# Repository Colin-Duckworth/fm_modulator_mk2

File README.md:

FM Modulator Project

This project is to make a colpitts oscillator based fm modulator from the transistor/component level.
It will consist of a common emitter, BJT amplifier, tapped LC tank (to form the oscillator), and emitter follower amp (as buffer) into an antenna feed

In terms of the toolchain, this will be an introduction for me to learn KiCad with its integrated SPICE simulation to build out the schematic.

## Projects

| Folder | Contents | Simulation |
|---|---|---|
| `project_folders/fm_modulator_openloop` | CE stage + tank, driven by an AC source | AC sweep |
| `project_folders/fm_modulator_closedloop` | Colpitts oscillator, RF buffer, varactor FM, mic + audio chain, power input (the board) | TRAN / FFT |

## BOM — `fm_modulator_closedloop` (JLCPCB assembly)

Stock and part type checked on jlcpcb.com on 2026-11-16. **Basic** parts have no setup fee; each unique **Extended** part adds a loading fee (about $3). The `LCSC` field on every symbol holds the part number, so the JLCPCB Tools / Fabrication Toolkit plugins can export the BOM and CPL directly.

| Designator | Qty | Value | Package / footprint | LCSC | Type | Part (manufacturer) | Notes |
|---|---|---|---|---|---|---|---|
| Q101, Q102 | 2 | MMBT3904 | SOT-23 | C20526 | Basic | MMBT3904 (CJ) | Oscillator + buffer; sim model = 2N3904 die |
| U1 | 1 | NE5532 | SOIC-8 | C7426 | Basic | NE5532DR (TI) | Dual op amp: mic diff amp + gain stage |
| U3 | 1 | AMS1117-3.3 | SOT-223 | C6186 | Basic | AMS1117-3.3 (AMS) | 3.3 V for the mic |
| D201 | 1 | SS14 | SMA (DO-214AC) | C2480 | Basic | SS14 (MDD) | Reverse-polarity protection |
| FB201 | 1 | 100 Ω @ 100 MHz | 0805 | C1015 | Basic | GZ2012D101TF (Sunlord) | Supply ferrite |
| R101, R104 | 2 | 510 Ω | 0603 | C23193 | Basic | 0603WAF5100T5E | Was 500 Ω (not a standard value) |
| R102 | 1 | 27 kΩ | 0603 | C22967 | Basic | 0603WAF2702T5E | |
| R103 | 1 | 10 kΩ | 0603 | C25804 | Basic | 0603WAF1002T5E | |
| R105 | 1 | 150 Ω | 0603 | C22808 | Basic | 0603WAF1500T5E | |
| R108 | 1 | 12 kΩ | 0603 | C22790 | Basic | 0603WAF1202T5E | |
| R109 | 1 | 2.7 kΩ | 0603 | C13167 | Basic | 0603WAF2701T5E | |
| R110 | 1 | 22 Ω | 0603 | C23345 | Basic | 0603WAF220JT5E | |
| R111 | 1 | 75 Ω | 0603 | C4275 | Basic | 0603WAF750JT5E | Was 68 Ω (68 Ω is Extended); buffer Ic ≈ 14 mA instead of 15 mA |
| R112 | 1 | 68 Ω | 0603 | C27592 | Extended | 0603WAF680JT5E | Buffer output termination: 68 Ω gives ≈50 Ω output once Cμ feedback is included (51 Ω gave ≈40 Ω) |
| R113 | 1 | 220 Ω | 0603 | C22962 | Basic | 0603WAF2200T5E | |
| R201 | 1 | 47 Ω | 0603 | C23182 | Basic | 0603WAF470JT5E | Audio supply RC filter |
| R202, R203 | 2 | 22 kΩ | 0603 | C31850 | Basic | 0603WAF2202T5E | VMID divider |
| R204, R206 | 2 | 5.1 kΩ | 0603 | C23186 | Basic | 0603WAF5101T5E | Diff amp inputs |
| R205, R207, R208 | 3 | 100 kΩ | 0603 | C25803 | Basic | 0603WAF1003T5E | |
| R209 | 1 | 3.3 kΩ | 0603 | C22978 | Basic | 0603WAF3301T5E | |
| C101, C102 | 2 | 47 pF C0G | 0603 | C1671 | Basic | CL10C470JB8NNNC | Were 50 p / 48 p |
| C103 | 1 | 22 pF C0G | 0603 | C1653 | Basic | CL10C220JB8NNNC | Was 33 p; trimmer now carries the rest |
| C104 | 1 | 33 pF C0G | 0603 | C1663 | Basic | CL10C330JB8NNNC | |
| C106 | 1 | 10 pF C0G | 0603 | C1634 | Basic | CL10C100JB8NNNC | Varactor coupling (was 1 p) |
| C110, C112, C203 | 3 | 1 nF X7R | 0603 | C1588 | Basic | CL10B102KB8NNNC | |
| C111, C202, C205, C209, C212 | 5 | 100 nF X7R | 0603 | C14663 | Basic | CC0603KRX7R9BB104 | |
| C210, C211 | 2 | 1 µF X5R | 0603 | C15849 | Basic | CL10A105KB8NNNC | Mic coupling |
| C201, C204, C206, C207, C213 | 5 | 10 µF 25 V X5R | 0805 | C15850 | Basic | CL21A106KAYNNNE | |
| C208 | 1 | 22 µF 25 V X5R | 0805 | C45783 | Basic | CL21A226MAQNNNE | AMS1117 output |
| C109 | 1 | 2.2 pF C0G | 0603 | C5137608 | Extended | FCC0603N2R2C500CT (FOJAN) | No Basic 2.2 pF exists |
| C105 | 1 | 5.8–20 pF trimmer | TZC3 (4.5×3.2) | C22468122 | Extended | STC3MD20-T1 (SEHWA) | Coarse frequency set (was fixed 3.3 p) |
| L101 | 1 | 1 µH ±5% | 0603 | C127458 | Extended | FHW0603UF1R0JST (FH) | SRF 400 MHz; most 1 µH 0603 parts self-resonate near 100 MHz |
| L102 | 1 | 100 nH ±2% wirewound | 0603 | C98088 | Extended | LQW18ANR10G00D (Murata) | Tank inductor; Q matters more than the setup fee |
| D101 | 1 | 1SV229 | SOD-323 | C2762682 | Extended | 1SV229(TPH3F) (Toshiba) | FM-band varactor |
| U2 | 1 | IM73A135V01 | PG-LLGA-5 (4×3) | C3171831 | Extended | IM73A135V01XTSA1 (Infineon) | Analog differential MEMS mic, bottom port (footprint has the sound hole) |
| RV201 | 1 | 50 kΩ trim | Bourns 3314J | C50895 | Extended | 3314J-1-503E (Bourns) | Deviation / audio gain |
| J1, J2 | 2 | SMA jack, vertical through-hole | Amphenol 132134 pattern (5 pins, 5.08 mm square) | C496549 | Extended | BWSMA-KE-Z001 (BAT Wireless) | J1 = ANT, J2 = TEST. About $0.40 each; JLC solders through-hole parts (wave/hand), or hand-solder them |
| U101 | 1 | PE4259 SPDT RF switch | SC-70-6 | C470892 | Extended | PE4259-63 (pSemi) | TX enable: CTRL high = RFC→RF1 (J1) |
| S101 | 1 | SPDT slide switch | SMD right-angle (Shouhan MSK12C02) | C431540 | Extended | MSK12C02 | STBY / TX, lever overhangs the right edge |
| D202 | 1 | Green LED | 0805 | C2297 | Basic | KT-0805G (KENTO) | PWR (on DC_Bias) |
| D102 | 1 | Red LED | 0603 | C2286 | Basic | KT-0603R (KENTO) | TX |
| R210 | 1 | 4.7 kΩ | 0603 | C23162 | Basic | 0603WAF4701T5E | PWR LED, ≈1.9 mA |
| R115, R117 | 2 | 1 kΩ | 0603 | C21190 | Basic | 0603WAF1001T5E | TX LED (≈1.3 mA); CTRL series resistor |
| R116 | 1 | 100 kΩ | 0603 | C25803 | Basic | 0603WAF1003T5E | TX_EN pull-down (STBY by default) |
| C113, C114 | 2 | 1 nF X7R | 0603 | C1588 | Basic | CL10B102KB8NNNC | PE4259 RF1/RF2 DC blocks |
| C115, C116 | 2 | 100 nF X7R | 0603 | C14663 | Basic | CC0603KRX7R9BB104 | U101 VDD decoupling; CTRL filter |
| TP3, TP4 | 2 | Test loop | Keystone 5015 SMD | C2906768 | **Hand-solder** | 5015 (Keystone) | MIC_IN, OPAMP_OUT; excluded from JLC BOM/CPL, order separately |
| TP5 | 1 | +12V_IN, red | Keystone 5010 THT | C2906765 | **Hand-solder** | 5010 (Keystone) | Alligator-clip power input; excluded from JLC BOM/CPL, order separately |
| TP6 | 1 | GND, black | Keystone 5011 THT | C238127 | **Hand-solder** | 5011 (Keystone) | Alligator-clip ground; excluded from JLC BOM/CPL, order separately |
| TP1 | 1 | Test pad | 1.0 mm pad | — | — | bare copper | No part to place (excluded from BOM/CPL) |
| R114, V101, V102 | — | — | — | — | — | — | **Simulation only**: excluded from BOM and board |

**Summary (Rev B):** JLC assembles 43 unique parts. 32 are Basic, covering all resistors except R112, all but one fixed capacitor, both transistors, the op amp, the LDO, the diode, the ferrite and both LEDs. 11 are Extended (C109, C105, L101, L102, D101, U2, RV201, J1/J2, R112, U101, S101), roughly $33 in setup fees. J1 and J2 are through-hole parts: JLC assembly adds a through-hole soldering charge, or leave them off the order and hand-solder them like the test loops. The four test loops (TP3–TP6) are hand-soldered: their footprints are on the board, but they're marked *exclude from BOM* and *exclude from position files* in KiCad, so JLC leaves the pads empty. Order them separately (LCSC numbers above, about 2× 5015, 1× 5010 red, 1× 5011 black). TP1 is a bare pad with no part.

## PCB — `fm_modulator_closedloop.kicad_pcb`

### Substrate and stackup (JLCPCB JLC04161H-7628, standard 4-layer FR-4)

| Layer | Use | Material | Thickness | εr |
|---|---|---|---|---|
| L1 — F.Cu | RF and oscillator traces, all parts | 1 oz copper | 0.035 mm | — |
| dielectric 1 | | 7628 prepreg | 0.2104 mm | 4.4 |
| L2 — In1.Cu "GND" | Solid ground plane (no routing) | 0.5 oz copper | 0.0152 mm | — |
| dielectric 2 | | FR-4 core | 1.065 mm | 4.6 |
| L3 — In2.Cu "PWR" | Power: DC_Bias plane + VCC_AUDIO plane | 0.5 oz copper | 0.0152 mm | — |
| dielectric 3 | | 7628 prepreg | 0.2104 mm | 4.4 |
| L4 — B.Cu | Control / audio / signal traces, GND pour | 1 oz copper | 0.035 mm | — |

Total ≈ 1.6 mm; HASL lead-free finish. In the JLC order choose **4 layers, 1.6 mm, Specify Stackup → JLC04161H-7628**.

### 50 Ω RF output (C112 → U101 → J1 / J2)
- **Geometry:** microstrip on L1 referenced to the L2 ground plane, h = 0.2104 mm, t = 0.035 mm, εr = 4.4.
- **Width:** Hammerstad–Jensen with thickness correction gives Z₀ = 50 Ω at **w = 0.373 mm** bare (51.0 Ω at 0.36 mm). Solder mask lowers Z₀ by about 1–2 Ω, so the RF traces are drawn at **0.36 mm** (≈ 50 Ω under mask). Confirm with JLC's impedance calculator before ordering.
- **Length:**
  - C112 → U101 RFC is about 11 mm, a straight run across the BUFFER AMP / TX SWITCH boundary.
  - Each throw (U101 → C113/C114 → J1/J2) is about 9 mm.
  - At 100 MHz that's under 2° (λg ≈ 1.68 m, ε_eff ≈ 3.19), so the lines are electrically short and the match is set by the source and load.
  - The source is the buffer: R112 = 68 Ω gives Z_out ≈ 50 Ω. With the switch's 0.35 dB loss and a 50 Ω load on J1/J2, everything is ≈ 50 Ω.
- **Ground:**
  - J1 and J2 are through-hole, so their four ground posts tie L1, L2 and L4 together right at the connector.
  - U101's GND pin has its own via beside the pin.
  - At these lengths, the L1 pour's normal 0.3 mm clearance to the RF traces has a negligible effect. The old rule-area keep-out and via fence went with the edge-launch connector.
- **Connectors:** J1 (ANT) and J2 (TEST) are vertical through-hole SMA jacks (BWSMA-KE-Z001) on the standard 5-pin pattern (centre pin plus four ground posts on a 5.08 mm square). The cable plugs in perpendicular to the board. The ~1.6 mm the centre pin runs through the stackup is about λ/1000 at 100 MHz, so it doesn't matter.

### Layout
- **Board:** 100 × 62 mm, four M3 mounting holes (3.2 mm NPTH) 3.5 mm in from each corner. Still within JLC's ≤ 100 × 100 mm price tier.
- **Floorplan** (re-laid 2026-11-18): five labelled silkscreen boxes. The top row is four 25 mm columns that follow the signal left → right, and a full-width POWER strip (about 16 mm) runs along the bottom.

  | Box | Parts | Notes |
  |---|---|---|
  | AUDIO (x 100–125) | U2 mic, C209, TP3, C210/C211, R204–R207, U1, C212, R209, C213, RV201, TP4, R202/R203/C206 (VMID) | Widely spaced for probing and rework. Mic at the top, U1 in the middle, AUDIO_OUT (RV201 / TP4) bottom-right facing R208. |
  | OSCILLATOR (x 125–150) | Q101, L101/R101, L102, C101–C106, R102–R105, TP1, D101, R208 | Kept tight (short tank loops), but spaced so no reference designators overlap. The tank output leaves at the bottom-right towards C109. |
  | BUFFER AMP (x 150–175) | C109, Q102, R108–R113, C110–C112 | Generous spacing. The RF line runs straight through at y = 127.5 mm. |
  | TX SWITCH & PORTS (x 175–200) | U101 + C113–C116, R116/R117, J2 TEST (top), J1 ANT (bottom), S101 + D102/R115 (red TX LED) | S101 sits on the right edge with its slider at the edge; silk reads STBY (top) / TX (bottom). |
  | POWER (bottom strip) | TP5 (+12 V) / TP6 (GND) clip posts, D201, FB201, C201–C203, D202 + R210 (green PWR LED), R201, C204/C205, C207, U3, C208 | Input on the right, flowing left: DC_Bias parts, then R201 at x = 150, then the VCC_AUDIO / 3V3 parts. |
- **Routing:**
  - **By script (L1):** RF only. That means the oscillator (including the varactor feed), the buffer, the tank → C109 link, and C112 → U101 → C113/C114 → J1/J2. Also U101's local nets (CTRL via C116/R117, VDD to C115, TX_EN R116 → R117) and GND / DC_Bias pad vias for the RF parts.
  - **By hand:** everything in AUDIO and POWER, plus the TX LED / S101 and the 3V3 and TX_EN runs to the switch column.
- **Vias:** each RF-part GND pad has its own via to L2, and each RF-part DC_Bias pad has a via to the L3 plane. GND stitching runs on a 4 mm grid inside the three RF boxes plus a ring around the board edge.
- **Pours:** L1 GND, L2 GND, L4 GND. L3 is split to match the sections:
  - **VCC_AUDIO:** under the AUDIO column plus the POWER strip left of x = 150 mm.
  - **DC_Bias:** everywhere else (under the OSCILLATOR, BUFFER and TX columns and the right half of the strip).
  - **R201** straddles the split at x = 150 mm in the strip.
- **Net classes:** RF (/RF_Out, /RF_Ant, /RF_Test, U101 RF1/RF2) 0.36 mm, Power (DC_Bias, VCC_AUDIO, 3V3) 0.5 mm, Default 0.25 mm.
- **JLC design rules:** 0.15 mm minimum track and clearance, 0.3/0.6 mm vias, 0.3 mm copper-to-edge.
- **Silkscreen, front:**
  - Five labelled section boxes.
  - Labels for +12V, GND, PWR, ANT (J1), TEST (J2) and STBY/TX at the switch.
  - Reference designators are 0.8 mm (meets the project's text-height rule), horizontal and clear of pads, with 0 silkscreen warnings.
- **Silkscreen, back:**
  - Each section has a short description sitting directly behind it.
  - The stackup (JLC04161H-7628 layer table + 50 Ω width) sits behind the oscillator / buffer boundary.
  - The power-path description and the project tag (name, date, Rev B) are in the POWER strip.

### Still to do in KiCad
DRC after the 2026-11-18 re-layout shows 0 copper/clearance errors, 0 silkscreen warnings and 0 schematic-parity issues. 47 unconnected items are left for hand routing.

1. **Route the non-RF nets.** Prefer L4 for anything crossing an RF box.
   - **Audio:** mic → C210/C211 → R204/R206 → U1, the U1 feedback nets, VMID, and AUDIO_OUT (U1 pin 7 / RV201 / TP4 → R208 in the oscillator box).
   - **Power:** TP5 → D201 → FB201 (wide, L1), DC_Bias and VCC_AUDIO plane vias for the POWER and AUDIO parts, and the PWR LED (R210 → D202).
   - **3V3:** U3 tab → C208 → C209 / U2 VDD, plus a run over to **C115 pad 1** (U101 VDD) and **S101 pin 1**.
   - **TX_EN:** S101 pin 2 → R115 (→ D102) and over to **R116 / R117** beside U101.
2. **Mic ground:** tie U2 pad 5 (centre GND) to pad 4.
3. **Refill zones** (B), then run DRC. The L3 VCC_AUDIO "isolated copper" warning clears once its pads have vias.
4. **Mic hole-clearance error:** one DRC error comes from the Infineon footprint itself (its centre GND pad sits 0.18 mm from its own sound hole). Exclude it in the DRC dialog.
5. **Check S101's direction with a meter** before the first power-up with an antenna: in the **TX** position, pins 2–1 should be connected. The red TX LED always shows the real state, because it hangs off TX_EN itself.
6. **Optional:** Update PCB from Schematic (F8) should report nothing to change; every footprint is linked to its symbol.

## Rev B: power LED and TX-enable switch

> **Status:** in the schematic and on the PCB (2026-11-18). Parts checked on jlcpcb.com on 2026-11-17/18; the PE4259 pinout and truth table were checked against the pSemi datasheet. The rows are in the BOM table above.

### Power indicator (green "PWR")
- **D202** (green 0805) + **R210** (4.7 kΩ) from `DC_Bias` to GND, in the POWER box.
- It sits after D201 and FB201, so it lights only when 12 V is present **and** the polarity is correct.
- Current: (11.65 V − ~2.9 V) / 4.7 kΩ ≈ **1.9 mA**. For a dimmer LED, raise R210 to 10 kΩ (≈ 0.9 mA).

### TX enable (SPDT RF switch after the buffer)
The oscillator and buffer **run all the time**, and only the buffer's output is steered. The tank therefore sees the same load in both positions, so the carrier doesn't jump when you go from tuning to transmitting. (Turning the buffer off instead would pull the carrier and leak 30–40 dB.)

```
                                     ┌─ RF1 ─ C113 1n ─ 50 Ω ─► J1  ANTENNA   (TX)
buffer ─ C112 ─ 50 Ω ─ RFC  U101 PE4259
                                     └─ RF2 ─ C114 1n ─ 50 Ω ─► J2  TEST      (STBY)
                       VDD ◄─ 3V3 (C115 100 nF)
                       CTRL ◄─ R117 1 kΩ ─┬─ TX_EN
                                          C116 100 nF to GND (debounce, keeps RF off the control line)

        3V3 ──o TX
               \___ S101 common ── TX_EN ──┬── R115 1 kΩ ── D102 red "TX" ── GND
        GND ──o STBY                       └── R116 100 kΩ ── GND (STBY if the switch is mid-travel)
```

- **The physical control:** **S101** is a small SMD slide switch (MSK12C02, right-angle). Its lever sticks out past the board edge, and the silkscreen reads **STBY ◄ ► TX**.
  - It drives `TX_EN` hard to 3V3 or GND, so no logic IC is needed.
  - The 100 kΩ pull-down means a broken switch or a mid-travel position defaults to STBY.
- **TX LED:** **D102** (red) hangs straight off `TX_EN`, so it lights exactly when the switch routes RF to the antenna. Current: (3.3 V − ~2.0 V) / 1 kΩ ≈ 1.3 mA.
- **RF switch:** **U101** is a pSemi PE4259: SPDT, 10 MHz–3 GHz, 0.35 dB insertion loss, ≥ 30 dB isolation (spec; typically more at 100 MHz), 1.8–3.3 V, with single-pin CMOS control.
  - **Pinout (SC-70-6):** 1 RF1, 2 GND, 3 RF2, 4 CTRL, 5 RFC, 6 VDD.
  - **Truth table (datasheet Table 5, VDD = 3 V):** CTRL high = RFC→RF1 (J1 antenna); CTRL low = RFC→RF2 (J2 test).
  - **DC blocking:** the datasheet requires RF pins 1, 3 and 5 to be DC-blocked. C112 blocks RFC; C113 and C114 block RF1 and RF2.
  - **Supply:** VDD comes from the 3V3 rail. The operating maximum is 3.3 V and the absolute maximum is 4.0 V, so the AMS1117's ±1–2 % tolerance is fine.
  - **Symbol:** the PE4259 symbol lives in the project library `fm_modulator.kicad_sym`, registered in the project `sym-lib-table`.
- **Test port:** **J2** is a second vertical through-hole SMA, the same part as J1, so it adds no extra Extended fee. In STBY the RF goes there, into a spectrum analyzer or SDR through an attenuator.
  - Keep a 50 Ω terminator on J2 when you're not measuring, so the buffer always sees 50 Ω.

### How you use it
1. Power up with S101 on **STBY**: green PWR on, red TX off.
2. J2 → 20–30 dB attenuator → analyzer/SDR. Set the carrier with C105 and the deviation with RV201 (±75 kHz).
3. Antenna on J1. Slide to **TX**: the red LED lights and RF goes to J1. The oscillator and buffer conditions don't change, so the carrier stays where you tuned it.
4. Slide back to STBY at any time.

Standby isn't absolute silence. About 30–40+ dB of the switch's isolation still leaks to J1, and the oscillator radiates slightly by itself; a shield can over the oscillator would reduce that. Transmit only on frequencies and at power levels you're permitted to use.

### Cost and load
- **Parts:** Rev B adds two new Extended parts (U101 and S101, about $6 in fees). J1 → BWSMA-KE-Z001 replaces the ~$5 Samtec edge-launch with a ~$0.40 part.
- **Load:** about 3.2 mA extra.
- **Simulation:** all Rev B parts are excluded from simulation. R114 (the 50 Ω simulation load) still sits on RF_Out, so the transient sim behaves as before.

## Design notes and calculations

All numbers below are hand estimates. Confirm them in the transient + FFT simulation.

### Power input
- 12 V on TP5/TP6 → **D201** (SS14, reverse-polarity protection, ~0.3–0.35 V drop at ~33 mA) → **FB201** + C201/C202/C203 → `DC_Bias` ≈ **11.65 V**.
- Current budget: oscillator ~5 mA + buffer ~14 mA + NE5532 ~8 mA + AMS1117 ground current ~5 mA + mic 0.17 mA + dividers → **≈ 33 mA**.
- `VCC_AUDIO` = DC_Bias through R201 (47 Ω, ~13.5 mA) ≈ **11.0 V**. R201 + C204 (corner ≈ 340 Hz) keep op-amp audio current ripple off the oscillator rail; supply ripple on the oscillator is FM noise (pushing).
- `VMID` = VCC_AUDIO / 2 ≈ **5.5 V** (R202/R203 + C206). It is both the op-amp DC operating point and the varactor's reverse bias.
- AMS1117-3.3 from 11.0 V: (11.0 − 3.3) V × ~5.4 mA ≈ 42 mW, which is fine for SOT-223.

### Tank sensitivity (how much a capacitor change moves the frequency)
- L102 = 100 nH at f₀ = 100 MHz → effective tank capacitance C_eff = 1 / ((2πf₀)²·L) = **25.3 pF**.
- The Colpitts pi network puts the collector-side capacitance C_c (C103 + C105 + ~3 pF transistor ≈ 38 pF) in series with the tank-side capacitance C_t (C104 + base branch + buffer + varactor branch). C_eff = C_c·C_t/(C_c+C_t) gives **C_t ≈ 76 pF**.
- A change at Tank_Output reaches C_eff scaled by (C_c/(C_c+C_t))² = (38/114)² = **0.111**.
- K_C = (f₀/2)·0.111/C_eff = 50 MHz × 0.111 / 25.3 pF ≈ **220 kHz per pF at Tank_Output**.
- **Calibrate this in simulation:** change C104 by 1 pF and measure the frequency shift. Every number below scales with it.

### Varactor (D101, 1SV229)
- Model `models/1SV229.lib`: C(V) = 39.9 pF / (1 + V/0.7)^0.665. This is a two-point fit to the listed specs (6.5 pF at 10 V, C2V/C10V = 2.5); check it against the datasheet curve.
- At VMID = 5.5 V: **C = 9.3 pF**, slope **dC/dV ≈ −1.0 pF/V**.
- Through C106 = 10 pF: branch capacitance = 10·9.3/19.3 = 4.8 pF. Its slope is (10/19.3)² × 1.0 = **0.27 pF/V**.
- **Modulator gain K_V = 220 kHz/pF × 0.27 pF/V ≈ 59 kHz/V.**
- **±75 kHz deviation needs 75/59 ≈ 1.27 V peak of audio on AUDIO_OUT.** The NE5532 can swing about ±3.5 V around 5.5 V on an 11 V supply, so the hard limit is about ±200 kHz. RV201 sets the operating level; very loud input will over-deviate.
- RF across the varactor: about 2 V peak on the tank, divided by C106 vs D101 to about 1 V peak on the diode. That stays well inside 5.5 V reverse bias, so the diode never conducts on RF peaks.

### Microphone and audio gain
- IM73A135V01: −38 dBV/Pa (differential) → 12.6 mV rms = **17.8 mV peak at 94 dB SPL (1 Pa)**.
- U1A differential amp: gain R207/R206 = 100k/5.1k = **19.6**, which rejects common-mode noise on the mic lines. The input high-pass (1 µF × 5.1 kΩ) is at 31 Hz.
- U1B non-inverting gain: 1 + RV201/R209 = **1 to 16.2**, with C213 setting DC gain to 1 so the output stays at VMID. Total gain is **19.6 to 318**.
- For ±75 kHz at 94 dB SPL: 1.27 V / (17.8 mV × 19.6) = 3.6 → **RV201 ≈ 8.7 kΩ**.
- At maximum gain (318), full deviation is reached at 1.27 V / 318 = 4.0 mV peak ≈ 0.22 Pa ≈ **81 dB SPL**, which is normal speech at about 10 cm. So RV201 covers full deviation from ~81 dB SPL (pot at max) to ~94 dB SPL (pot at ~8.7 kΩ).
- Possible additions: 75 µs (US) / 50 µs (EU) pre-emphasis in U1B's feedback, and a ~15 kHz low-pass to limit occupied bandwidth.

### Why ±75 kHz and not ±1 MHz deviation
- **Receivers:** broadcast FM uses ±75 kHz deviation on 200 kHz channel spacing, and receiver IF filters are about 150–250 kHz wide. With ±1 MHz the occupied bandwidth (Carson's rule) is 2 × (1 MHz + 15 kHz) ≈ **2 MHz, about 10 channels**. A receiver would only catch the signal as it swept through its IF, giving clipped, distorted audio and interference outside the allowed band.
- **Circuit:** ±1 MHz with ±3.5 V of swing needs K_V ≈ 285 kHz/V, i.e. about 1.3 pF/V at Tank_Output. That exceeds the 1SV229's entire slope at 5.5 V (1.0 pF/V) even with C106 removed. Getting there would need a low bias voltage (where 2 V of RF would forward-bias the diode) or several varactors, and the C–V curvature would then add percent-level audio distortion.
- **Where 1 MHz makes sense is tuning range.** The C105 trimmer (5.8–20 pF) moves C_c from about 31 pF to 45 pF, i.e. C_eff from 21.9 to 28.3 pF, giving roughly **95–107 MHz**. That's about ±6 MHz of channel selection, with ±75 kHz of audio FM on top.

### Simulation notes (closed loop)
- U1, U2, U3, RV201, D201, FB201, the test points and J1 are excluded from simulation (no SPICE models). **V102** (simulation only) stands in for the op-amp output: `dc=5.5` biases the varactor. Set `ampl=1.27 f=200k` to see FM sidebands in the FFT. Use a 200 kHz test tone because a 1 kHz tone needs milliseconds of 100 MHz simulation.
- V101 (simulation only) still provides the 0 → 12 V power-on ramp on DC_Bias.
- ERC shows two `lib_symbol_mismatch` warnings for MMBT3904. They're cosmetic; "Update symbol from library" clears them, but re-check the Sim fields afterwards (`Sim.Library models/2N3904.lib`, `Sim.Name 2N3904`, `Sim.Pins 1=B 2=E 3=C`).

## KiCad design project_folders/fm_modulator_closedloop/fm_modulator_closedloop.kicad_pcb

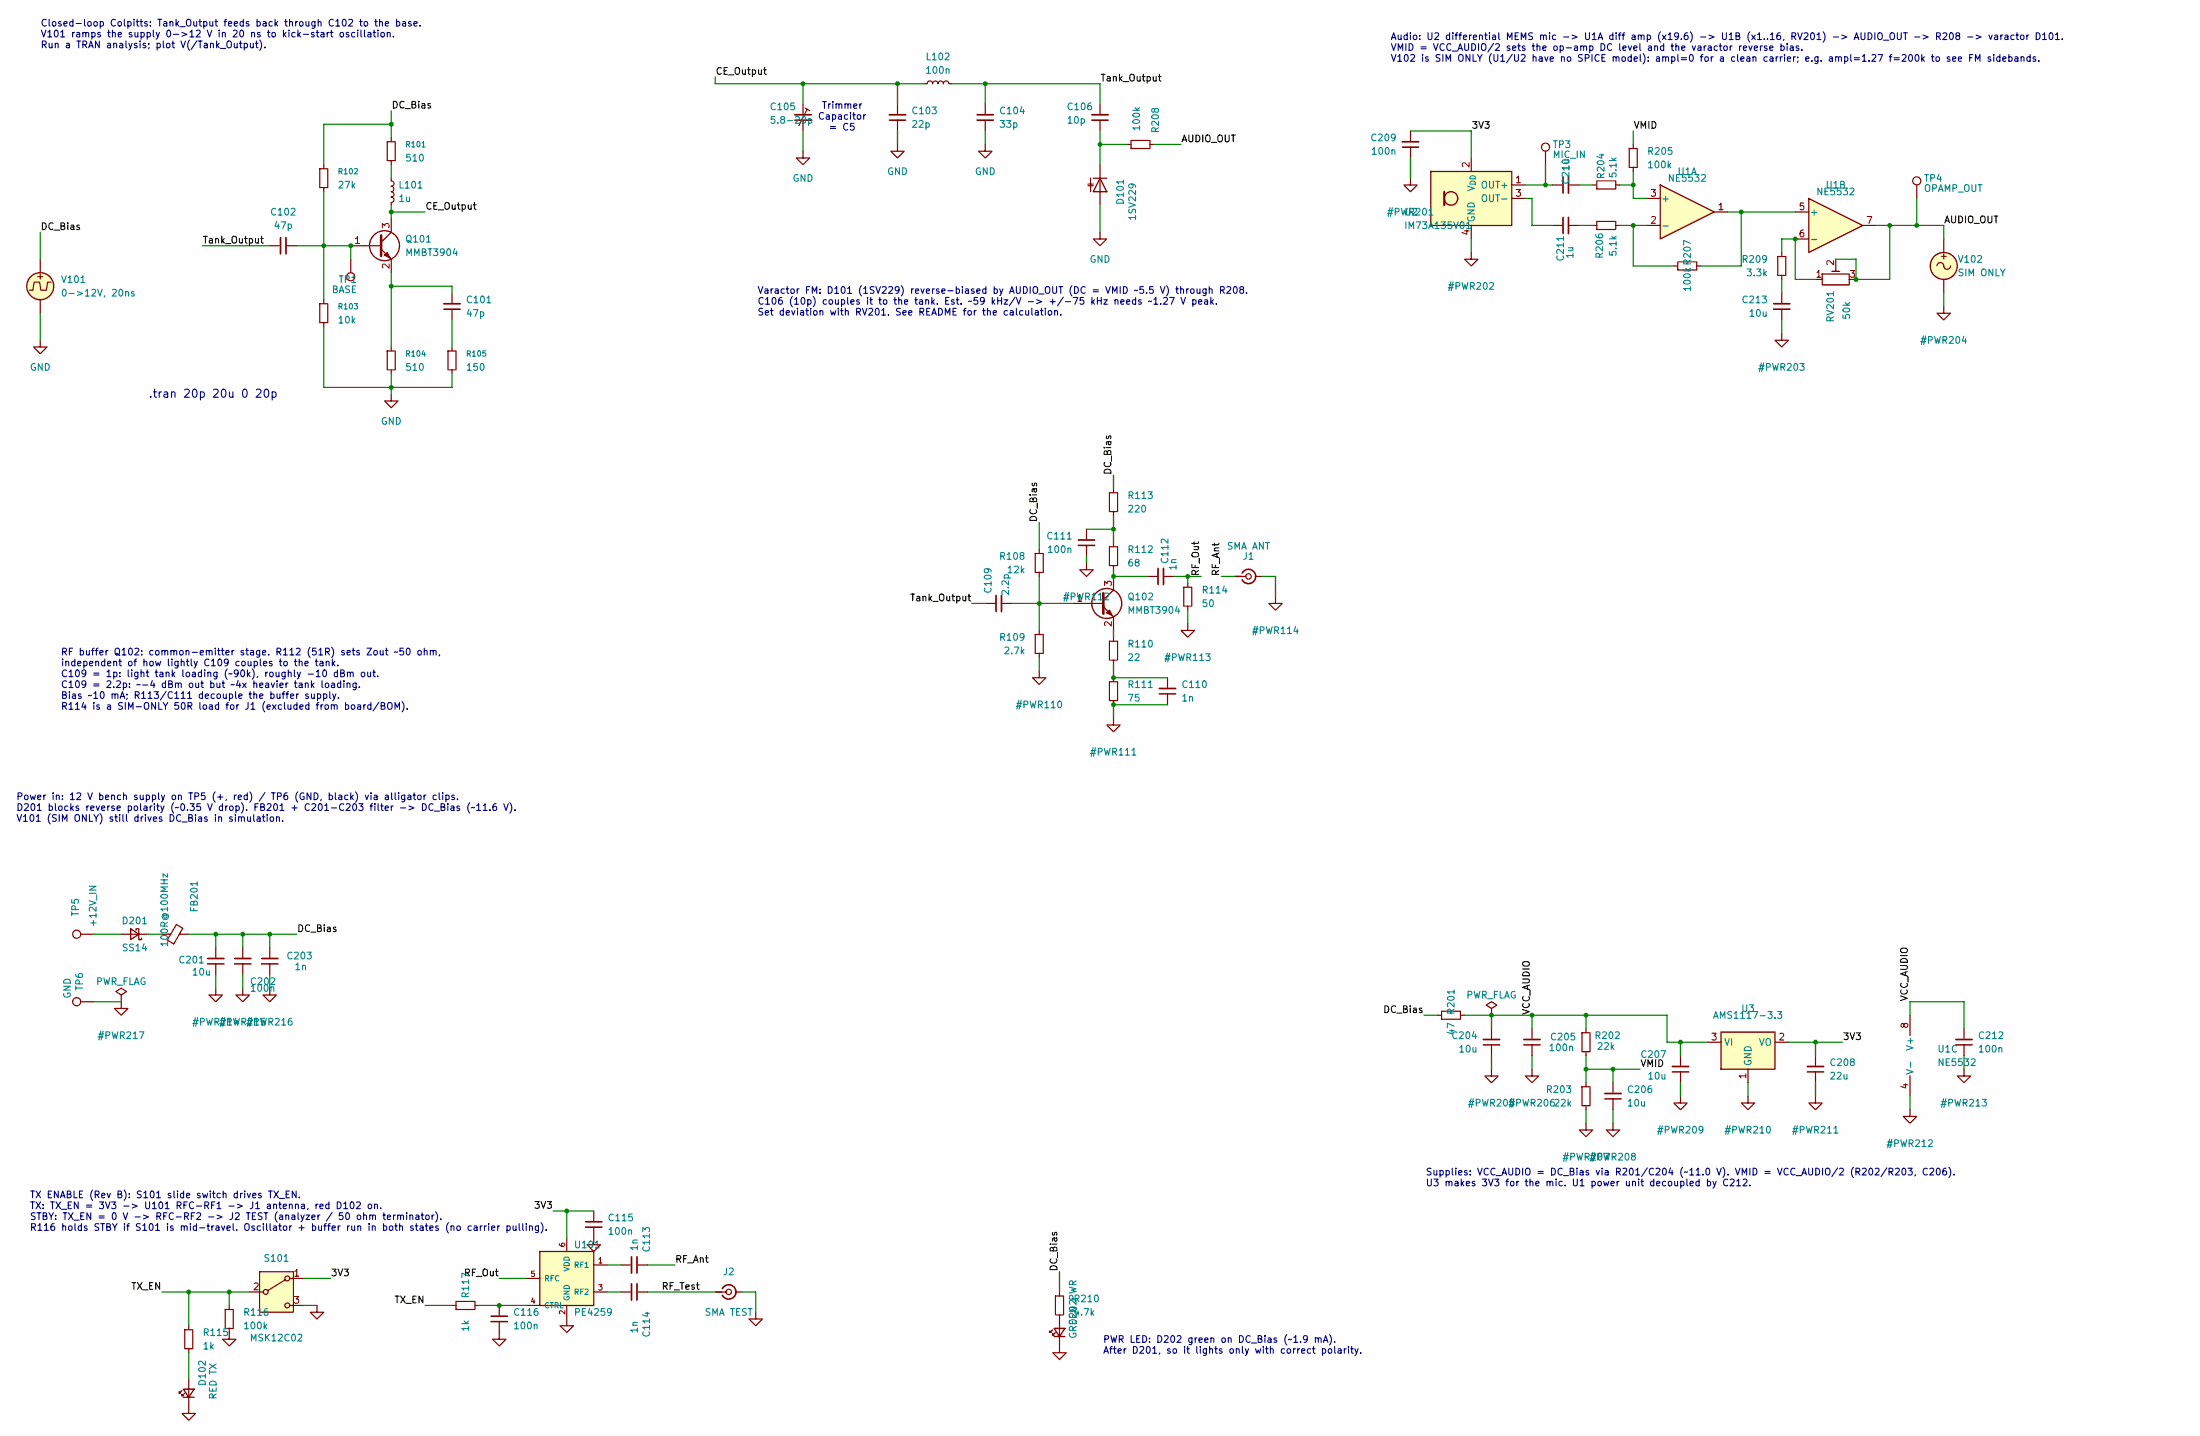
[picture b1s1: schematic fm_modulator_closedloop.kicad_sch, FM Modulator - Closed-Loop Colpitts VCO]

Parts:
C101, C102: 47p; C_0603_1608Metric; LCSC C1671
C103: 22p; C_0603_1608Metric; LCSC C1653
C104: 33p; C_0603_1608Metric; LCSC C1663
C105: 5.8-20p; C_Trimmer_Murata_TZC3; LCSC C22468122
C106: 10p; C_0603_1608Metric; LCSC C1634
C109: 2.2p; C_0603_1608Metric; LCSC C5137608
C110, C112, C113, C114, C203: 1n; C_0603_1608Metric; LCSC C1588
C111, C115, C116, C202, C205, C209, C212: 100n; C_0603_1608Metric; LCSC C14663
C201, C204, C206, C207, C213: 10u; C_0805_2012Metric; LCSC C15850
C208: 22u; C_0805_2012Metric; LCSC C45783
C210, C211: 1u; C_0603_1608Metric; LCSC C15849
D101: 1SV229; D_SOD-323; LCSC C2762682
D102: RED TX; LED_0603_1608Metric; LCSC C2286
D201: SS14; D_SMA; LCSC C2480
D202: GREEN PWR; LED_0805_2012Metric; LCSC C2297
FB201: 100R@100MHz; L_0805_2012Metric; LCSC C1015
J1: SMA ANT; SMA_Amphenol_132134_Vertical; LCSC C496549
J2: SMA TEST; SMA_Amphenol_132134_Vertical; LCSC C496549
L101: 1u; L_0603_1608Metric; LCSC C127458
L102: 100n; L_0603_1608Metric; LCSC C98088
Q101, Q102: MMBT3904; SOT-23; LCSC C20526
R101, R104: 510; R_0603_1608Metric; LCSC C23193
R102: 27k; R_0603_1608Metric; LCSC C22967
R103: 10k; R_0603_1608Metric; LCSC C25804
R105: 150; R_0603_1608Metric; LCSC C22808
R108: 12k; R_0603_1608Metric; LCSC C22790
R109: 2.7k; R_0603_1608Metric; LCSC C13167
R110: 22; R_0603_1608Metric; LCSC C23345
R111: 75; R_0603_1608Metric; LCSC C4275
R112: 68; R_0603_1608Metric; LCSC C27592
R113: 220; R_0603_1608Metric; LCSC C22962
R114: 50
R115, R117: 1k; R_0603_1608Metric; LCSC C21190
R116, R205, R207, R208: 100k; R_0603_1608Metric; LCSC C25803
R201: 47; R_0603_1608Metric; LCSC C23182
R202, R203: 22k; R_0603_1608Metric; LCSC C31850
R204, R206: 5.1k; R_0603_1608Metric; LCSC C23186
R209: 3.3k; R_0603_1608Metric; LCSC C22978
R210: 4.7k; R_0603_1608Metric; LCSC C23162
RV201: 50k; Potentiometer_Bourns_3314J_Vertical; LCSC C50895
S101: MSK12C02; SW_SPDT_Shouhan_MSK12C02; LCSC C431540
TP1: BASE; TestPoint_Pad_D1.0mm
TP3: MIC_IN; TestPoint_Keystone_5015_Micro_Mini; LCSC C2906768
TP4: OPAMP_OUT; TestPoint_Keystone_5015_Micro_Mini; LCSC C2906768
TP5: +12V_IN; TestPoint_Keystone_5010-5014_Multipurpose; LCSC C2906765
TP6: GND; TestPoint_Keystone_5010-5014_Multipurpose; LCSC C238127
U1: NE5532; SOIC-8_3.9x4.9mm_P1.27mm; LCSC C7426
U2: IM73A135V01; Infineon_PG-LLGA-5-2; LCSC C3171831
U3: AMS1117-3.3; SOT-223-3_TabPin2; LCSC C6186
U101: PE4259; SOT-363_SC-70-6; LCSC C470892
V101: 0->12V, 20ns
V102: SIM ONLY

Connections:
/3V3: C115.1, C208.1, C209.1, S101.1 (A), U2.2 (V_{DD}), U3.2 (VO), U101.6 (VDD)
/AUDIO_OUT: R208.2, RV201.2, RV201.3, TP4.1, U1.7, V102.1
/CE_Output: C103.1, C105.1, L101.2, L102.1, Q101.3 (C)
/DC_Bias: C201.1, C202.1, C203.1, FB201.2, R101.1, R102.1, R108.1, R113.1, R201.1, R210.1, V101.1
/RF_Ant: C113.2, J1.1 (In)
/RF_Out: C112.2, R114.1, U101.5 (RFC)
/RF_Test: C114.2, J2.1 (In)
/TX_EN: R115.1, R116.1, R117.1, S101.2 (B)
/Tank_Output: C102.1, C104.1, C106.1, C109.1, L102.2
/VCC_AUDIO: C204.1, C205.1, C207.1, C212.1, R201.2, R202.1, U1.8 (V+), U3.3 (VI)
/VMID: C206.1, R202.2, R203.1, R205.1
GND: C103.2, C104.2, C105.2, C110.2, C111.2, C115.2, C116.2, C201.2, C202.2, C203.2, C204.2, C205.2, C206.2, C207.2, C208.2, C209.2, C212.2, C213.2, D101.2 (A), D102.1 (K), D202.1 (K), J1.2 (Ext), J2.2 (Ext), R103.2, R104.2, R105.2, R109.2, R111.2, R114.2, R116.2, R203.2, S101.3 (C), TP6.1, U1.4 (V-), U2.4 (GND), U2.5 (GND), U3.1 (GND), U101.2 (GND), V101.2, V102.2
unnamed: C101.2, R105.1
unnamed: C110.1, R110.2, R111.1
unnamed: C111.1, R112.1, R113.2
unnamed: C210.2, R204.1
unnamed: C211.2, R206.1
unnamed: C213.1, R209.2
unnamed: C106.2, D101.1 (K), R208.1
unnamed: D102.2 (A), R115.2
unnamed: D201.2 (A), TP5.1
unnamed: D201.1 (K), FB201.1
unnamed: D202.2 (A), R210.2
unnamed: L101.1, R101.2
unnamed: C102.2, Q101.1 (B), R102.2, R103.1, TP1.1
unnamed: C101.1, Q101.2 (E), R104.1
unnamed: C109.2, Q102.1 (B), R108.2, R109.1
unnamed: C112.1, Q102.3 (C), R112.2
unnamed: Q102.2 (E), R110.1
unnamed: R204.2, R205.2, U1.3 (+)
unnamed: R206.2, R207.1, U1.2 (-)
unnamed: R207.2, U1.1, U1.5 (+)
unnamed: R209.1, RV201.1, U1.6 (-)
unnamed: C210.1, TP3.1, U2.1 (OUT+)
unnamed: C211.1, U2.3 (OUT-)
unnamed: C116.1, R117.2, U101.4 (CTRL)
unnamed: C113.1, U101.1 (RF1)
unnamed: C114.1, U101.3 (RF2)

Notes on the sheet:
Power in: 12 V bench supply on TP5 (+, red) / TP6 (GND, black) via alligator clips. D201 blocks reverse polarity (~0.35 V drop). FB201 + C201-C203 filter -> DC_Bias (~11.6 V). V101 (SIM ONLY) still drives DC_Bias in simulation.
RF buffer Q102: common-emitter stage. R112 (51R) sets Zout ~50 ohm, independent of how lightly C109 couples to the tank. C109 = 1p: light tank loading (~90k), roughly -10 dBm out. C109 = 2.2p: ~-4 dBm out but ~4x heavier tank loading. Bias ~10 mA; R113/C111 decouple the buffer supply. R114 is a SIM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
Trimmer Capacitor = C5
Audio: U2 differential MEMS mic -> U1A diff amp (x19.6) -> U1B (x1..16, RV201) -> AUDIO_OUT -> R208 -> varactor D101. VMID = VCC_AUDIO/2 sets the op-amp DC level and the varactor reverse bias. V102 is SIM ONLY (U1/U2 have no SPICE model): ampl=0 for a clean carrier; e.g. ampl=1.27 f=200k to see FM 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
Supplies: VCC_AUDIO = DC_Bias via R201/C204 (~11.0 V). VMID = VCC_AUDIO/2 (R202/R203, C206). U3 makes 3V3 for the mic. U1 power unit decoupled by C212.
Varactor FM: D101 (1SV229) reverse-biased by AUDIO_OUT (DC = VMID ~5.5 V) through R208. C106 (10p) couples it to the tank. Est. ~59 kHz/V -> +/-75 kHz needs ~1.27 V peak. Set deviation with RV201. See README for the calculation.
PWR LED: D202 green on DC_Bias (~1.9 mA). After D201, so it lights only with correct polarity.
TX ENABLE (Rev B): S101 slide switch drives TX_EN. TX: TX_EN = 3V3 -> U101 RFC-RF1 -> J1 antenna, red D102 on. STBY: TX_EN = 0 V -> RFC-RF2 -> J2 TEST (analyzer / 50 ohm terminator). R116 holds STBY if S101 is mid-travel. Oscillator + buffer run in both states (no carrier pulling).
.tran 20p 20u 0 20p
Closed-loop Colpitts: Tank_Output feeds back through C102 to the base. V101 ramps the supply 0->12 V in 20 ns to kick-start oscillation. Run a TRAN analysis; plot V(/Tank_Output).

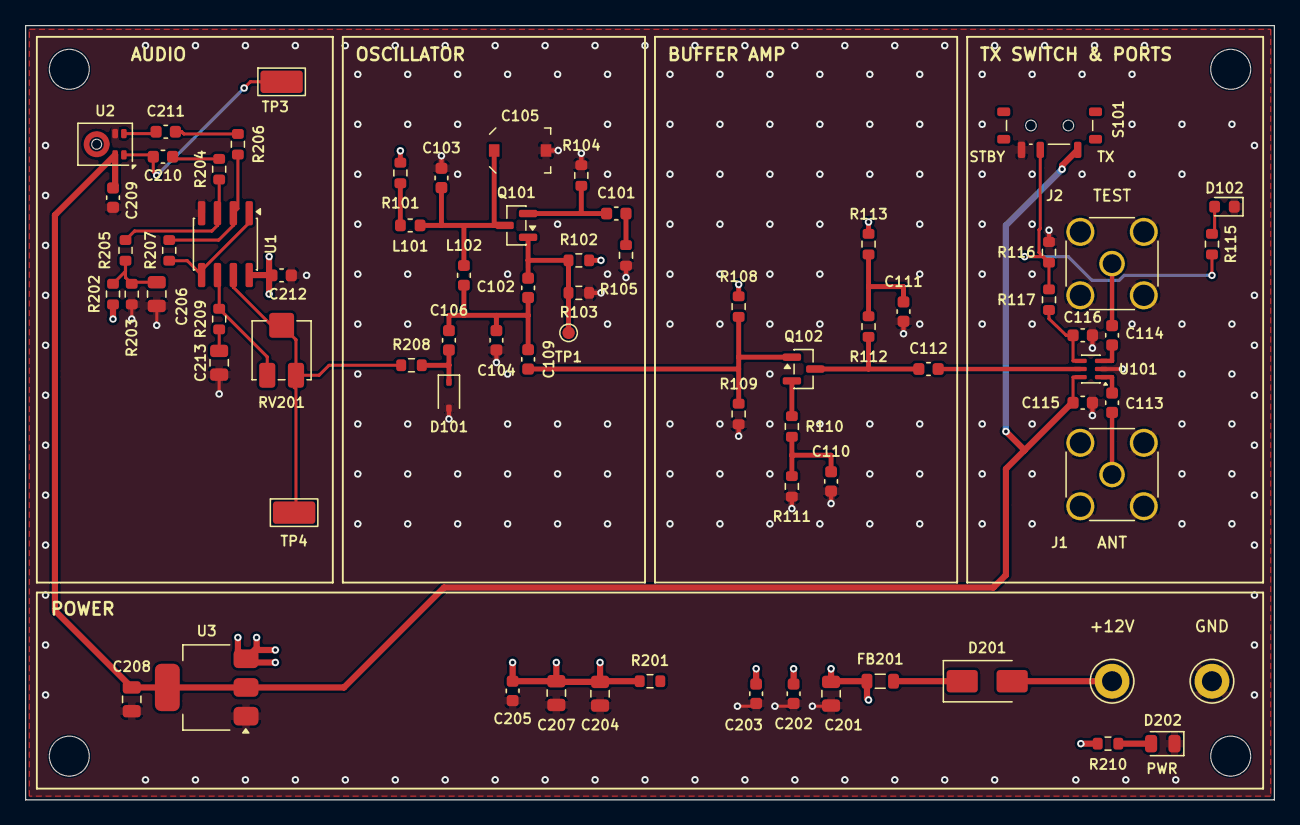
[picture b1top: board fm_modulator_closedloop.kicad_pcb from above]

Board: 4 copper layers, 100.0 x 62.0 mm, 77 parts (0 on the bottom side), 38 nets.

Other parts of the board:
H1, H2, H3, H4: M3; MountingHole_3.2mm_M3
